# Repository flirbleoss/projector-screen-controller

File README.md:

# Projector Screen Controller

Simple controller for basic motorized projector screens. An _almost_-drop-in
replacement for the Da-Lite SCB-100.

Status: _Work in progress_

# Background

Tired of the commercial screen controller letting out its magic smoke every
couple of years and not content with the $400 replacement cost, I decided to
make my own _almost_-drop-in replacement with more emphasis on electronic
protection than the commercial variant seems to have.

In my analysis of both SCB-100s that failed, it appeared a transient condition
upset the MAX232 driver such that it causes a dead-short between the 5v and 0v
rails. The charge pump capacitors of the MAX232 chip are adjacent to the
ULN2003 relay driver and the 12V decoupling capacitor. The design relies on
the diodes in the ULN2003 for back-EMF suppression, which I speculate may not
be adequate for the off-brand relays in use in both of my SCB-100s (an online
search reveals other specimens have relays from a more reputable brand,
however.) Finally, the switching power supply module is soldered to the back
of the logic board. While there is a plastic divider between the boards, there
is only a few milimeters of space and line voltage spikes may well cause
interference; additionally there are several places where line voltage and
signal voltage traces come closer than I would be comfortable with.

It is my conclusion therefore that the failures are likely caused by
insufficient physical isolation and insufficient transient back-EMF
suppression.

## Design objectives

* Same form-factor for the board, so it can use the same metal case
  in-situ.
* Connections in roughly the same locations, with the same pin ordering.
* Use removable Phoenix connectors with screw terminals throughout.
* Improved electronic protection;
  * Better flyback suppression from the relays.
  * DC power protection in case the power supply fails.
  * Physical board isolation (with board cut-outs) between line voltages
    and the 5V/12V sections, especially around the relays.
  * Better isolation between 12V and 5V sections, to avoid relay noise
    issues.
  * Modern high-efficiency switching power supply with plenty of
    protection features.
* More indicator LEDs to show what is going on.
* Backward-compatible RS232 protocol, but enhancements to allow
  customizing, for example, the motor run time.
* Open-source design.

# Implementation

## Preview

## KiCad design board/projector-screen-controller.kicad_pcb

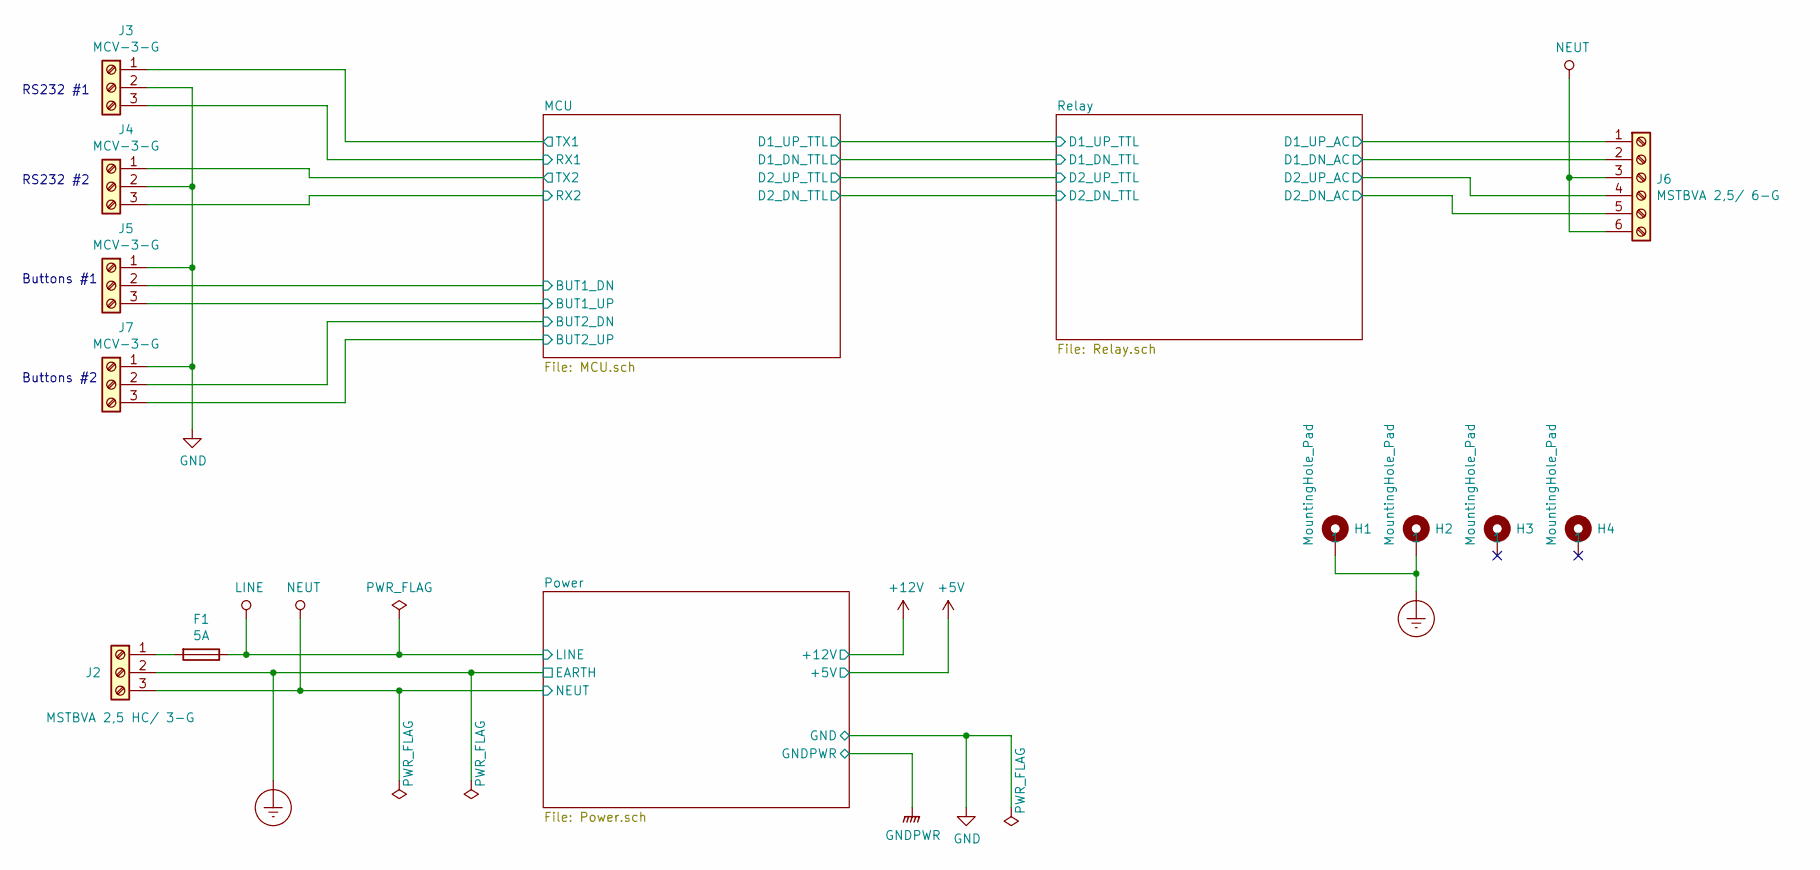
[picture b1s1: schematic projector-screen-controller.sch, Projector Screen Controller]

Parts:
F1: 5A; Fuseholder5x20_horiz_open_inline_Type-I
H1, H2, H3, H4: MountingHole_Pad; MountingHole_3.7mm_Pad_Via
J2: MSTBVA 2,5 HC/ 3-G; PhoenixContact_MSTBVA_2,5_3-G_1x03_P5.00mm_Vertical; mpn 1924208
J3, J4, J5, J7: MCV-3-G; PhoenixContact_MCV_1,5_3-G-3.5_1x03_P3.50mm_Vertical; mpn 1843619
J6: MSTBVA 2,5/ 6-G; PhoenixContact_MSTBVA_2,5_6-G_1x06_P5.00mm_Vertical; mpn 1755558

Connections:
/MCU/BUT1_DN: J5.2; also elsewhere on the board
/MCU/BUT1_UP: J5.3; also elsewhere on the board
/MCU/BUT2_DN: J7.2; also elsewhere on the board
/MCU/BUT2_UP: J7.3; also elsewhere on the board
/MCU/RX1: J3.3; also elsewhere on the board
/MCU/RX2: J4.3; also elsewhere on the board
/MCU/TX1: J3.1; also elsewhere on the board
/MCU/TX2: J4.1; also elsewhere on the board
/Relay/D1_DN_AC: J6.2; also elsewhere on the board
/Relay/D1_UP_AC: J6.1; also elsewhere on the board
/Relay/D2_DN_AC: J6.5; also elsewhere on the board
/Relay/D2_UP_AC: J6.4; also elsewhere on the board
Earth_Protective: H1.1, H2.1, J2.2; also elsewhere on the board
GND: J3.2, J4.2, J5.1, J7.1; also elsewhere on the board
LINE: F1.1; also elsewhere on the board
NEUT: J2.3, J6.3, J6.6; also elsewhere on the board
unnamed: F1.2, J2.1

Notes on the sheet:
RS232 #1
RS232 #2
Buttons #1
Buttons #2

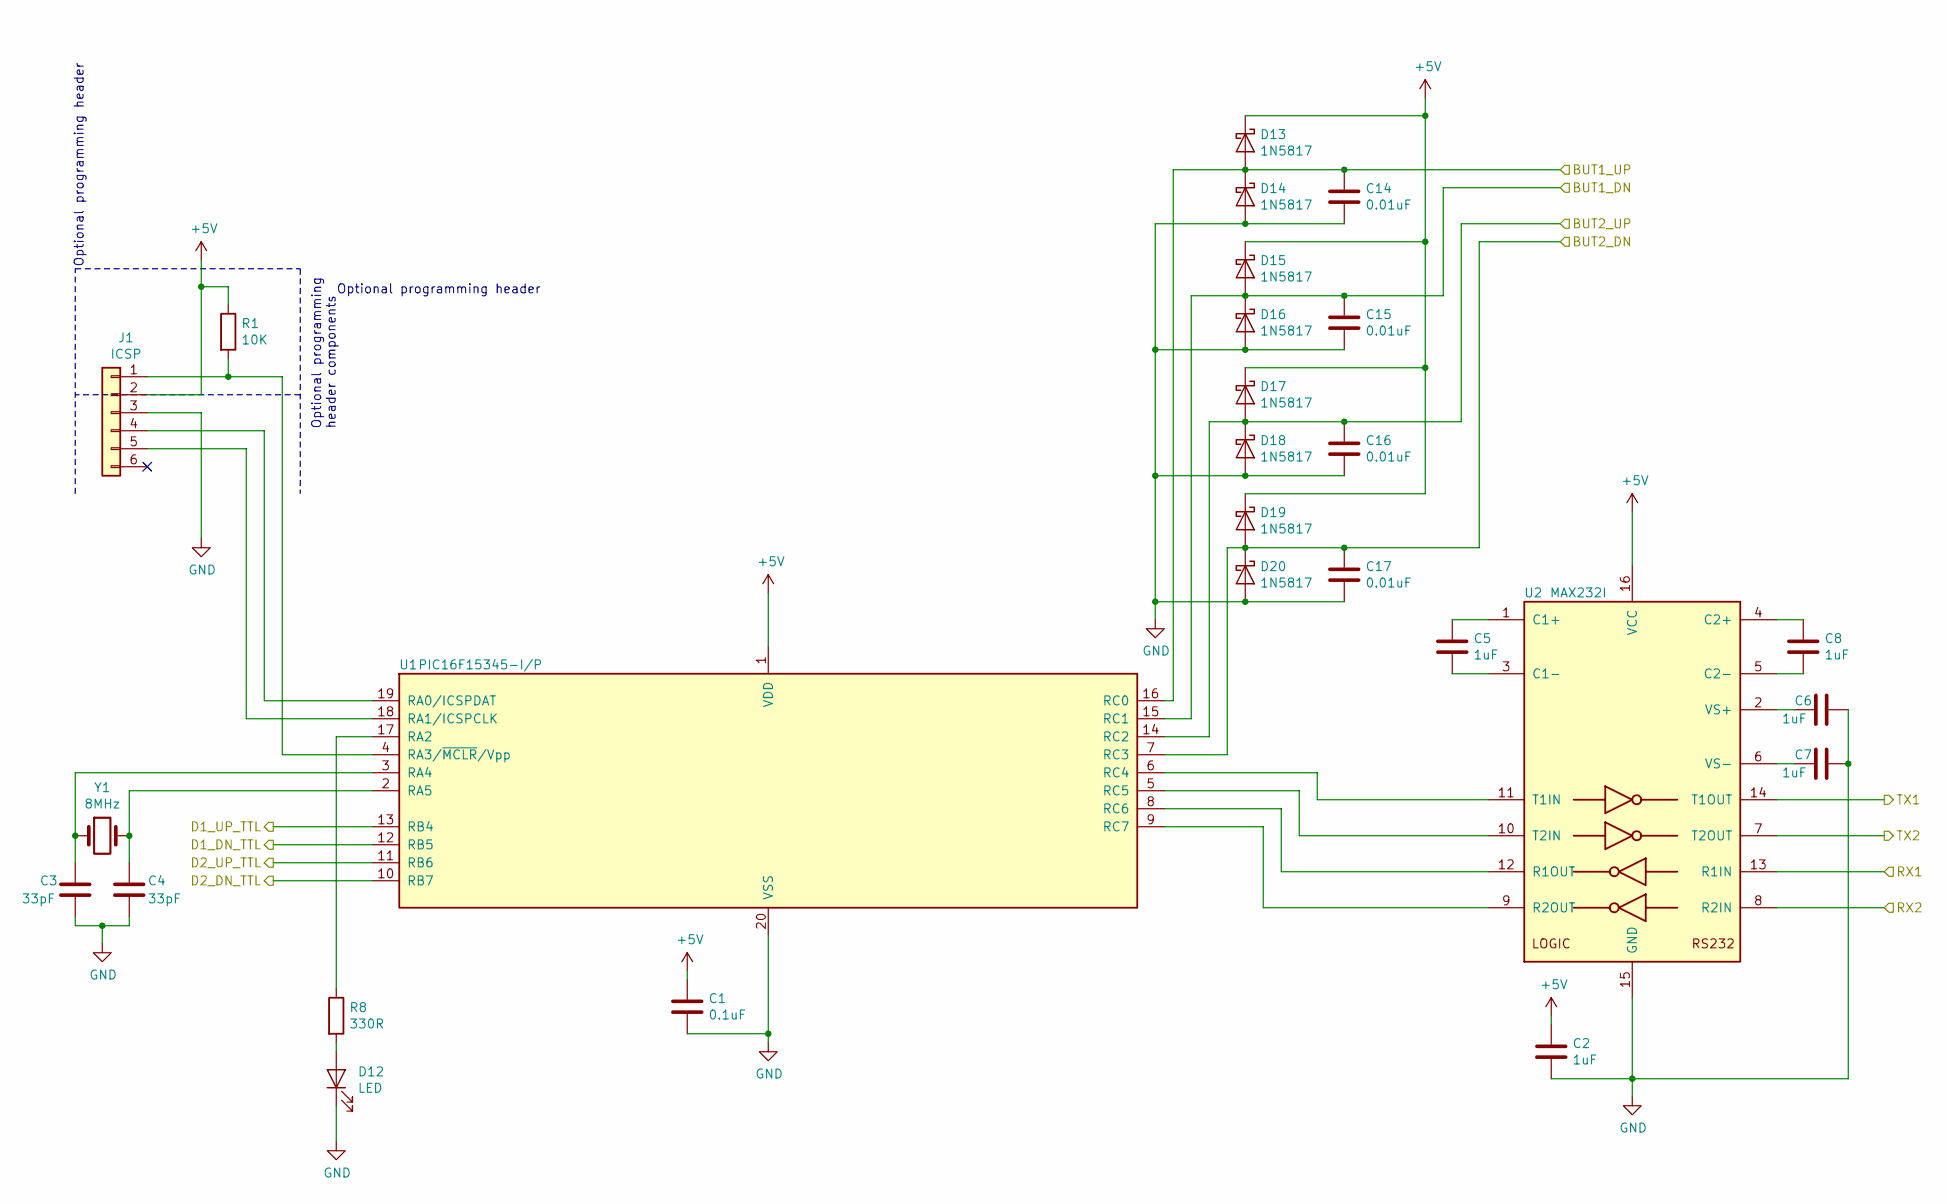
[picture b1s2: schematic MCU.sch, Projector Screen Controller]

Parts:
C1: 0.1uF; C_Disc_D5.0mm_W2.5mm_P2.50mm
C2, C5, C6, C7, C8: 1uF; C_Disc_D5.0mm_W2.5mm_P2.50mm
C3, C4: 33pF; C_Disc_D5.0mm_W2.5mm_P2.50mm; mpn FG18C0G1H330JNT06
C14, C15, C16, C17: 0.01uF; C_Disc_D5.0mm_W2.5mm_P2.50mm
D12: LED; LED_D3.0mm
D13, D14, D15, D16, D17, D18, D19, D20: 1N5817; D_DO-41_SOD81_P2.54mm_Vertical_KathodeUp
J1: ICSP; PINHEAD1-6
R1: 10K; R_Axial_DIN0207_L6.3mm_D2.5mm_P10.16mm_Horizontal
R8: 330R; R_Axial_DIN0207_L6.3mm_D2.5mm_P10.16mm_Horizontal
U1: PIC16F15345-I/P; DIP-20_W7.62mm_LongPads; mpn PIC16F15345-I/P
U2: MAX232I; DIP-16_W7.62mm_LongPads; mpn MAX232IN
Y1: 8MHz; Crystal_HC49-4H_Vertical; mpn XT9S20ANA8M

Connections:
+5V: C1.1, C2.1, D13.1 (K), D15.1 (K), D17.1 (K), D19.1 (K), J1.2, R1.1, U1.1 (VDD), U2.16 (VCC); also elsewhere on the board
/MCU/BUT1_DN: C15.1, D15.2 (A), D16.1 (K), U1.15 (RC1); also elsewhere on the board
/MCU/BUT1_UP: C14.1, D13.2 (A), D14.1 (K), U1.16 (RC0); also elsewhere on the board
/MCU/BUT2_DN: C17.1, D19.2 (A), D20.1 (K), U1.7 (RC3); also elsewhere on the board
/MCU/BUT2_UP: C16.1, D17.2 (A), D18.1 (K), U1.14 (RC2); also elsewhere on the board
/MCU/D1_DN_TTL: U1.12 (RB5); also elsewhere on the board
/MCU/D1_UP_TTL: U1.13 (RB4); also elsewhere on the board
/MCU/D2_DN_TTL: U1.10 (RB7); also elsewhere on the board
/MCU/D2_UP_TTL: U1.11 (RB6); also elsewhere on the board
/MCU/RX1: U2.13 (R1IN); also elsewhere on the board
/MCU/RX2: U2.8 (R2IN); also elsewhere on the board
/MCU/TX1: U2.14 (T1OUT); also elsewhere on the board
/MCU/TX2: U2.7 (T2OUT); also elsewhere on the board
GND: C1.2, C2.2, C3.2, C4.2, C6.1, C7.1, C14.2, C15.2, C16.2, C17.2, D12.1 (K), D14.2 (A), D16.2 (A), D18.2 (A), D20.2 (A), J1.3, U1.20 (VSS), U2.15 (GND); also elsewhere on the board
unnamed: C3.1, U1.3 (RA4), Y1.1
unnamed: C4.1, U1.2 (RA5), Y1.2
unnamed: C5.1, U2.1 (C1+)
unnamed: C5.2, U2.3 (C1-)
unnamed: C6.2, U2.2 (VS+)
unnamed: C7.2, U2.6 (VS-)
unnamed: C8.1, U2.4 (C2+)
unnamed: C8.2, U2.5 (C2-)
unnamed: D12.2 (A), R8.2
unnamed: J1.1, R1.2, U1.4 (RA3/~MCLR~/Vpp)
unnamed: J1.4, U1.19 (RA0/ICSPDAT)
unnamed: J1.5, U1.18 (RA1/ICSPCLK)
unnamed: R8.1, U1.17 (RA2)
unnamed: U1.5 (RC5), U2.10 (T2IN)
unnamed: U1.6 (RC4), U2.11 (T1IN)
unnamed: U1.8 (RC6), U2.12 (R1OUT)
unnamed: U1.9 (RC7), U2.9 (R2OUT)

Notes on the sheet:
Optional programming header
Optional programming header components

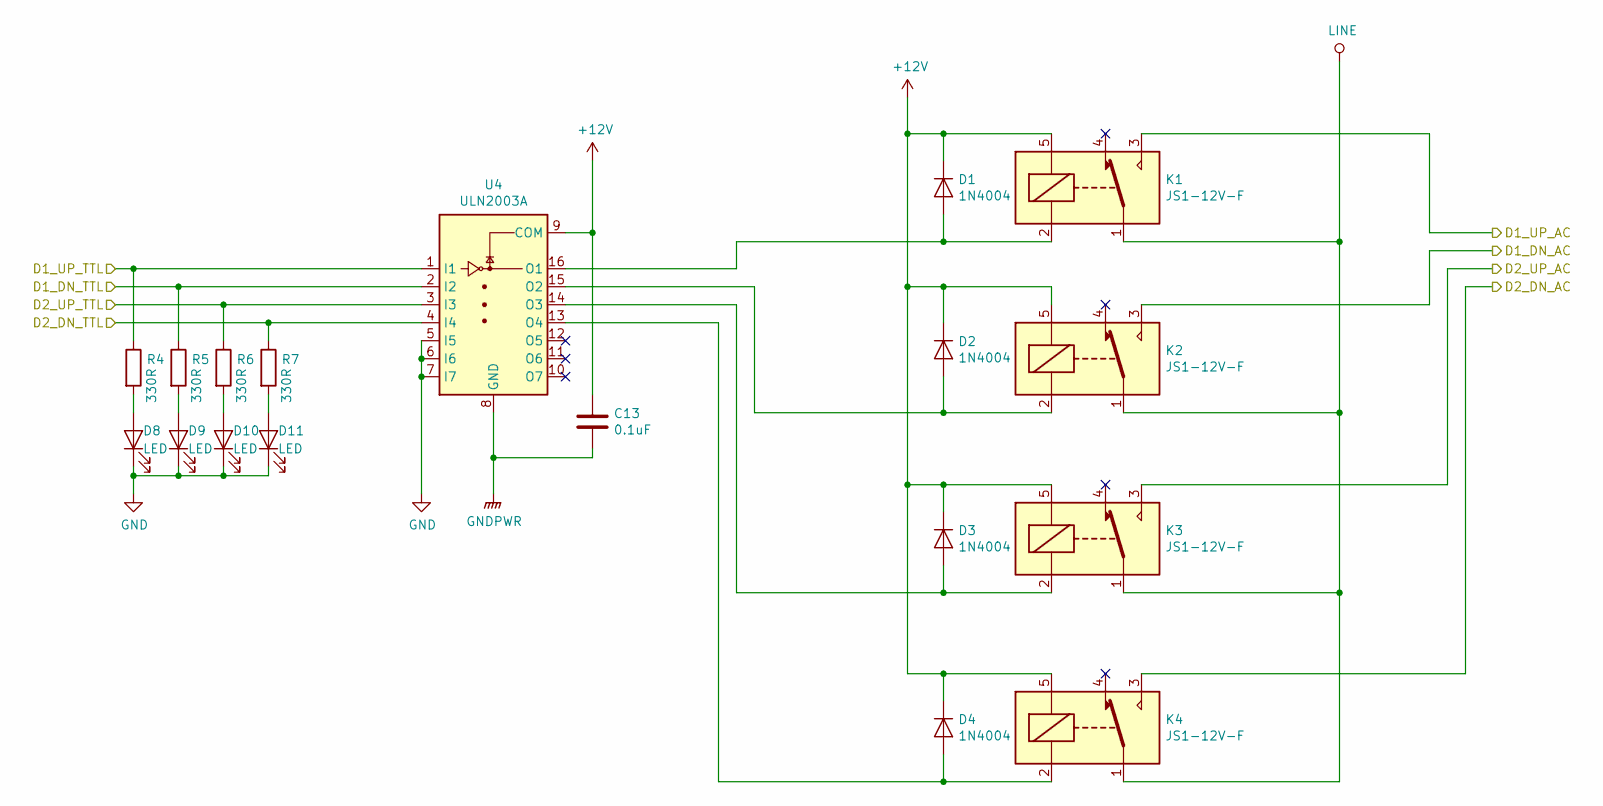
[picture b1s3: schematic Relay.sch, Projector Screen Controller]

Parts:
C13: 0.1uF; C_Disc_D5.0mm_W2.5mm_P2.50mm
D1, D2, D3, D4: 1N4004; D_DO-41_SOD81_P10.16mm_Horizontal
D8, D9, D10, D11: LED; LED_D3.0mm
K1, K2, K3, K4: JS1-12V-F; Relay_SPDT_SANYOU_SRD_Series_Form_C; mpn JS1-12V-F
R4, R5, R6, R7: 330R; R_Axial_DIN0207_L6.3mm_D2.5mm_P10.16mm_Horizontal
U4: ULN2003A; DIP-16_W7.62mm_LongPads; mpn ULN2003A

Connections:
+12V: C13.1, D1.1 (K), D2.1 (K), D3.1 (K), D4.1 (K), K1.5, K2.5, K3.5, K4.5, U4.9 (COM); also elsewhere on the board
/MCU/D1_DN_TTL: R5.1, U4.2 (I2); also elsewhere on the board
/MCU/D1_UP_TTL: R4.1, U4.1 (I1); also elsewhere on the board
/MCU/D2_DN_TTL: R7.1, U4.4 (I4); also elsewhere on the board
/MCU/D2_UP_TTL: R6.1, U4.3 (I3); also elsewhere on the board
/Relay/D1_DN_AC: K2.3; also elsewhere on the board
/Relay/D1_UP_AC: K1.3; also elsewhere on the board
/Relay/D2_DN_AC: K4.3; also elsewhere on the board
/Relay/D2_UP_AC: K3.3; also elsewhere on the board
GND: D8.1 (K), D9.1 (K), D10.1 (K), D11.1 (K), U4.5 (I5), U4.6 (I6), U4.7 (I7); also elsewhere on the board
GNDPWR: C13.2, U4.8 (GND); also elsewhere on the board
LINE: K1.1, K2.1, K3.1, K4.1; also elsewhere on the board
unnamed: D1.2 (A), K1.2, U4.16 (O1)
unnamed: D2.2 (A), K2.2, U4.15 (O2)
unnamed: D3.2 (A), K3.2, U4.14 (O3)
unnamed: D4.2 (A), K4.2, U4.13 (O4)
unnamed: D8.2 (A), R4.2
unnamed: D9.2 (A), R5.2
unnamed: D10.2 (A), R6.2
unnamed: D11.2 (A), R7.2

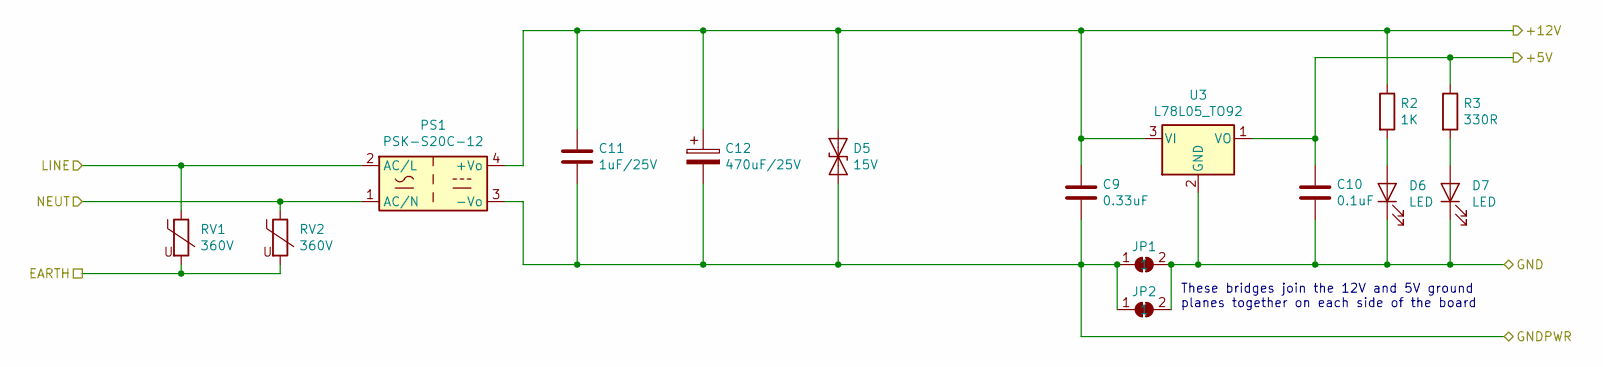
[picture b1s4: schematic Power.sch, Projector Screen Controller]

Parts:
C9: 0.33uF; C_Disc_D5.0mm_W2.5mm_P2.50mm; mpn FG18X7R1H334KRT00
C10: 0.1uF; C_Disc_D5.0mm_W2.5mm_P2.50mm; mpn FG18X7R1H104KNT06
C11: 1uF/25V; C_Disc_D5.0mm_W2.5mm_P2.50mm; mpn FG18X7R1E105KRT00
C12: 470uF/25V; CP_Radial_D10.0mm_P2.50mm_P5.00mm; mpn UPW1E471MPD
D5: 15V; D_DO-41_SOD81_P12.70mm_Horizontal; mpn 1.5KE15CA-E3/54
D6, D7: LED; LED_D3.0mm
JP1, JP2: SolderJumper_2_Bridged; SolderJumper-2_P1.3mm_Bridged2Bar_RoundedPad1.0x1.5mm
PS1: PSK-S20C-12; ACDC-Conv_CUI-PSK-S20C; mpn PSK-S20C-12
R2: 1K; R_Axial_DIN0207_L6.3mm_D2.5mm_P10.16mm_Horizontal
R3: 330R; R_Axial_DIN0207_L6.3mm_D2.5mm_P10.16mm_Horizontal
RV1, RV2: 360V; RV_Disc_D15.5_W7.2_P7.5; mpn VDRS14T230BSE
U3: L78L05_TO92; TO-92L; mpn L78L05ABZ-TR

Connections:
+5V: C10.1, R3.1, U3.1 (VO); also elsewhere on the board
+12V: C9.1, C11.1, C12.1, D5.1 (A1), PS1.4 (+Vo), R2.1, U3.3 (VI); also elsewhere on the board
Earth_Protective: RV1.2, RV2.2; also elsewhere on the board
GND: C10.2, D6.1 (K), D7.1 (K), JP1.2 (B), JP2.2 (B), U3.2 (GND); also elsewhere on the board
GNDPWR: C9.2, C11.2, C12.2, D5.2 (A2), JP1.1 (A), JP2.1 (A), PS1.3 (-Vo); also elsewhere on the board
LINE: PS1.2 (AC/L), RV1.1; also elsewhere on the board
NEUT: PS1.1 (AC/N), RV2.1; also elsewhere on the board
unnamed: D6.2 (A), R2.2
unnamed: D7.2 (A), R3.2

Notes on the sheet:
These bridges join the 12V and 5V ground planes together on each side of the board

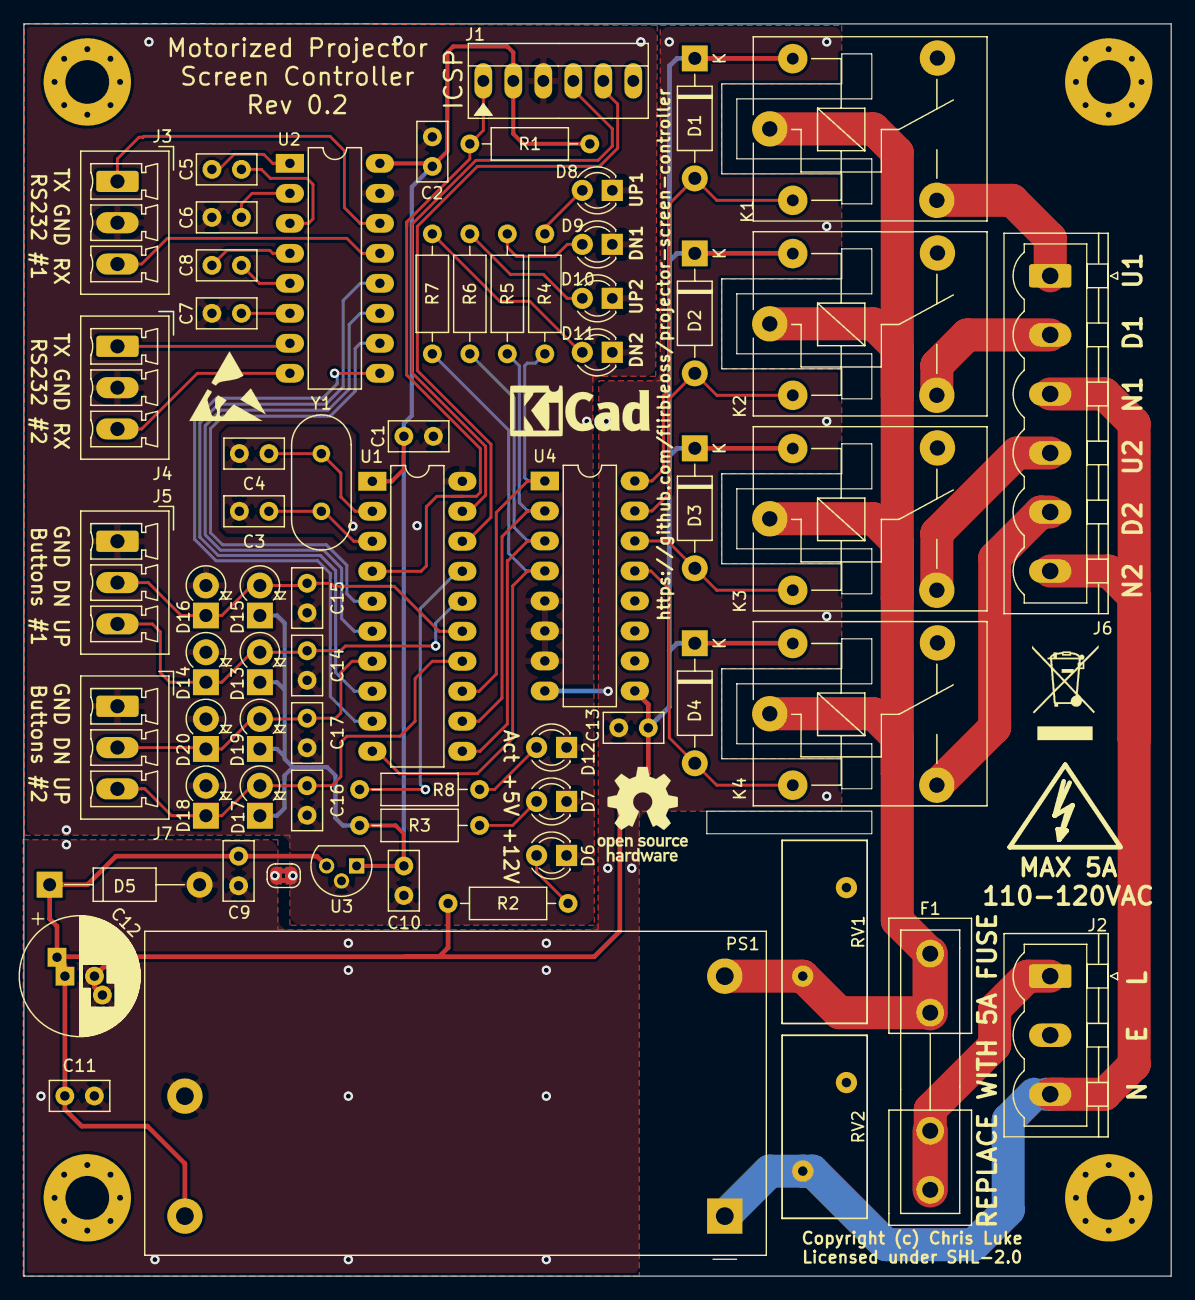
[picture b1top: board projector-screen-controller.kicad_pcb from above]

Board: 2 copper layers, 97.1 x 106.0 mm, 71 parts (1 on the bottom side), 51 nets.

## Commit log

2019-08-31 Projector Screen Controller
    - Basic schematic and board layout
2019-09-01 Add button 2, LEDs, TVS diode
    * Add button 2; rewire to match the prototype
    * Add a TVS diode across the 12V rail; value TBD
    * Rework power nets into the power sheet; don't use the globals
    inside the sheet, expose the rails as pins.
    * Move power protection inside the power sheet.
    * Add power LEDs
2019-09-01 Update README, add ground planes, adjust clearance
    * Update the README with background and a 3d preview image.
    * Add ground planes to front and back of logic section; add an earth plane on
    back of line voltage section.
    * Check clearances around line voltage input section.
    * Change mounting holes to a standard type with plated flange.
2019-09-02 Add Solderpad SHL-2.0 license
2019-09-02 Update fuse footprint, add more 3d models, update TODO
2019-09-02 Add relay status LEDs
2019-09-02 Add nominal LED R values; ground plane tweaks; first board spin
2019-09-02 Bump revision to 0.2
2019-09-02 Skeleton firmware
    * Basic hardware initialization
    * Template for interrupt handling
    * Details over timers, etc still needs to be worked out
2019-09-02 Basic UART handling
    * Circular buffers for TX and RX, for UART1 and UART2
    * Wiring for TX and RX on UART interrupts
    * Basic primitives for writing to and reading from buffers
    * Not tested yet
2019-09-03 Update tools to latest versions
2019-09-03 UART size fix
    * Off-by-one in one comparison
2019-09-07 Minor layout tweaks, component updates
    * Add an MCU driven status LED
    * Update LED current limit resistor values
    * Minor trace tweaks for clearance
    * Based on empirical measurements of rev 0.1 board, adjust the location of the
    board mounting holes.
2019-09-07 UART fixes; test code
    * UART tweaks;
    * Disable ADCs (pin thieves!)
    * Add missing BRG16 flag
    * Be complete about the PPS setup (though empirically not necessary)
    * Manage interrupts around some critical code
    * Add simple test code to the main loop;
2019-09-08 Split the 5v and 12v ground paths
    * To control the return path for (noisy) relay current, split the grounds for
    the 12v and 5v sections.
    * The grounds are joined by bridges (solder pads) placed adjacent to the 5v
    regulator, on both layers.
    * The gound plane is split in two; conveniently the 12v vs 5v components were
    already well placed to make this straightforward.
2019-09-08 Add a smattering of ground vias
2019-09-08 First approximation of a working system
    - Working relay control, with timed shutoff
    - Working serial command input with basic feedback
    - Note: No button control yet
    - Now a C99 compliant project (previously was xc8's interpretation of C90)
    - Bugfix in UART FIFO; off-by-one on buffer put rollover
    - Wrapped unused function in ifdef for now to cease a warning
2019-09-08 Update board symbols, minor ground plane fixes
    * Fuse rating, board maximums
    * ESD logo
    * WEEE logo
    * Some ground plane fixes around the MAX232
2019-09-09 First approximation of button handling
    - De-bounce input lines by effectively comparing the input line at both
    time interrupt time and after a short timer expires.
    - Reset the timer if any input line triggers. It's a short period, but
    the assumption is that 'stop' is the combination of the 'up' and
    'down' buttons and there may be a short delay before both lines are
    engaged; so long as it's less than the de-bounce interval then we will
2019-09-09 Fix KiCad 4 footprints
    * Update the Phoenix connectors with KiCad 5 footprints
2019-09-11 Update all footprints to KiCad 5 paths
    * All footprints updated.
    * 3D models for the relays seem to be missing from KiCad, however, so I
    have a copy in my personal library. Mostly cosmetic.
2019-09-11 Minor cleanup to layout
2019-09-13 Button read fixes
    * Properly initialize timer 0; enable it and TMR0 is not a 16-bit overlay
    of the L and H sections so reset those independently
    * We want the falling edge; sense is not inverted like other platforms
    * Likewise, need to invert the port read, since it's active low; oddity here
    though, bitwise-invert (~) works in the straight assignment case (a = ~b)
    but will not compile in a slightly more involved expression (a = b & ~c) -
2019-09-13 Channel 2 buttons are reversed; fix in code
2019-09-13 Serial protocol tweaks
    * Add serial reports, to both UARTs, whenever button presses result in
    action
    * Ignore all non-printable characters received
2019-09-13 Fix channel 2 button reversal
    * The hierarchical schematic pins for channel 2 buttons were reversed in the
    root schematic. Correct this, and add board revision logic to the firmware so
    board versions can be targeted by the build.
2019-09-13 Update gerbers; minor layout tweaks
    * Add ICSP text next to ISCP header
    * Better spacing around channel 2 button traces
    * Update 3d preview, gerbers and board PDF
2019-09-14 Rework the PIC configuration to use keywords
    * Turns out keywords can be used for PIC configuration values, and the IDE
    config tool will tell you what these words are; shame they're not in the
    datasheet, really.
2019-09-14 Add a simple clock diagnostic
    * Dump various system clock statuses
    * Adds a way to use stdlib stdio on UART 1
2019-09-14 Relay reporting after button presses and timer expiration
    * Use a flag to signal relay reporting to the UARTS
    * Report after button presses have been executed
    * Report when relays turn off at timer expiration
2019-09-14 Workaround for potential compiler bug
    * The ctypes macros for detecting ASCII character class seem to confuse the
    compiler into not generating code for them. By undefining the 'isprint'
    macro we fall-through to the stdlib implementation instead.
2019-09-14 Timer cleanup
    * Rework some of the timer management. This started as an exercise in reducing
    compiler warnings at the highest setting (though that proved fruitless when it
    came to type size reduction to __bit values). Instead ended up breaking out some
    of the timer management macros for better control of what is going on. Still a
    slight inconsistency between Timer0 and Timer1, but nothing egregious.
2019-09-18 Adjust ground plane clearance, LED margin clearances
    * For PCB DRC checks, fix clearances.
    * Make AC section tracks slightly larger.
2019-09-18 Add/correct a bunch of part numbers
2019-09-21 Layout adjustments to make room
    * Move the relays and diodes left to give a little more room to the
    power connectors; adjust ground planes to suit, etc.
    * Larger footprint for TVS diode; related adjustments.
    * Other minor adjustments to layout.
    * Add board-only preview.
2019-09-21 Update gerbers and PDFs
2019-09-22 Via tweaks; update earth flood
    * Tweak some via locations.
    * Update some of the earth flood fill around relay pins that was missed
    previously.
2019-09-22 Fix receiving on UART 2
    * Typo in the control polling loop; was checing UART_1 twice and UART_2
    not at all.
    * Use enum types for UART channels and control serial units, to
    improve type checking.
    * Bump to firmware version 0.2.
2019-09-23 Update xtal load capacitors, fix left mounting holes
    * Try some 33pF caps for the crystal.
    * Reflect the left side mounting holes in the schematic.
    * Reroute one RS232 TTL line; though now more stuff runs under the clock
    lines so may move all the RS232 TTL traces later.
2019-09-28 Make room for input filtering
    * Move the crystal block up and isolate its ground plane.
    * Route the RS232 TTL signals around the crystal block.
    * Update images, PDFs and gerbers.
2019-09-28 First pass at input protection for buttons
    * Schottky diodes & capacitors to limit and smooth the inputs.
    * Relies on the WPU of the MCU to provide a charge for the C (possibly
    a bad idea, will see).
    * Had to move a bunch of stuff to make room and make sure the ground paths
    were sensible.
    * Update all the disc capacitors to the Kicad 5 footprint.

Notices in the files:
board/MCU.sch:
Copyright (c) 2019 Chris Luke; licensed under SHL-2.0
board/projector-screen-controller.kicad_pcb:
Copyright (c) Chris Luke
